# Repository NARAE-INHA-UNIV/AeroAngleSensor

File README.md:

# AeroAngleSensor

[[Youtube] 무인 항공기용 회전각 센서 시현 영상](https://www.youtube.com/watch?v=Au1dN9QMTIA)

- 일시 : 2025 1학기
- 팀명 : 항공전자, 각도발전소(인하종합설계경진대회)
- 팀장 : 김정걸
- 팀원 : 김성호, 임정섭, 이해강, 이현제

## 프로젝트 구조

```
AeroAngleSensor/
├── AeroAngleSense        # KiCAD 회로
├── AeroAngleSense.step   # 센서 step 파일
├── docs                  # docs 문서 및 이미지 에셋
├── Firmware              # 펌웨어 STM32 코드
├── LICENSE.md
├── README.md
└── Schematic.pdf
```

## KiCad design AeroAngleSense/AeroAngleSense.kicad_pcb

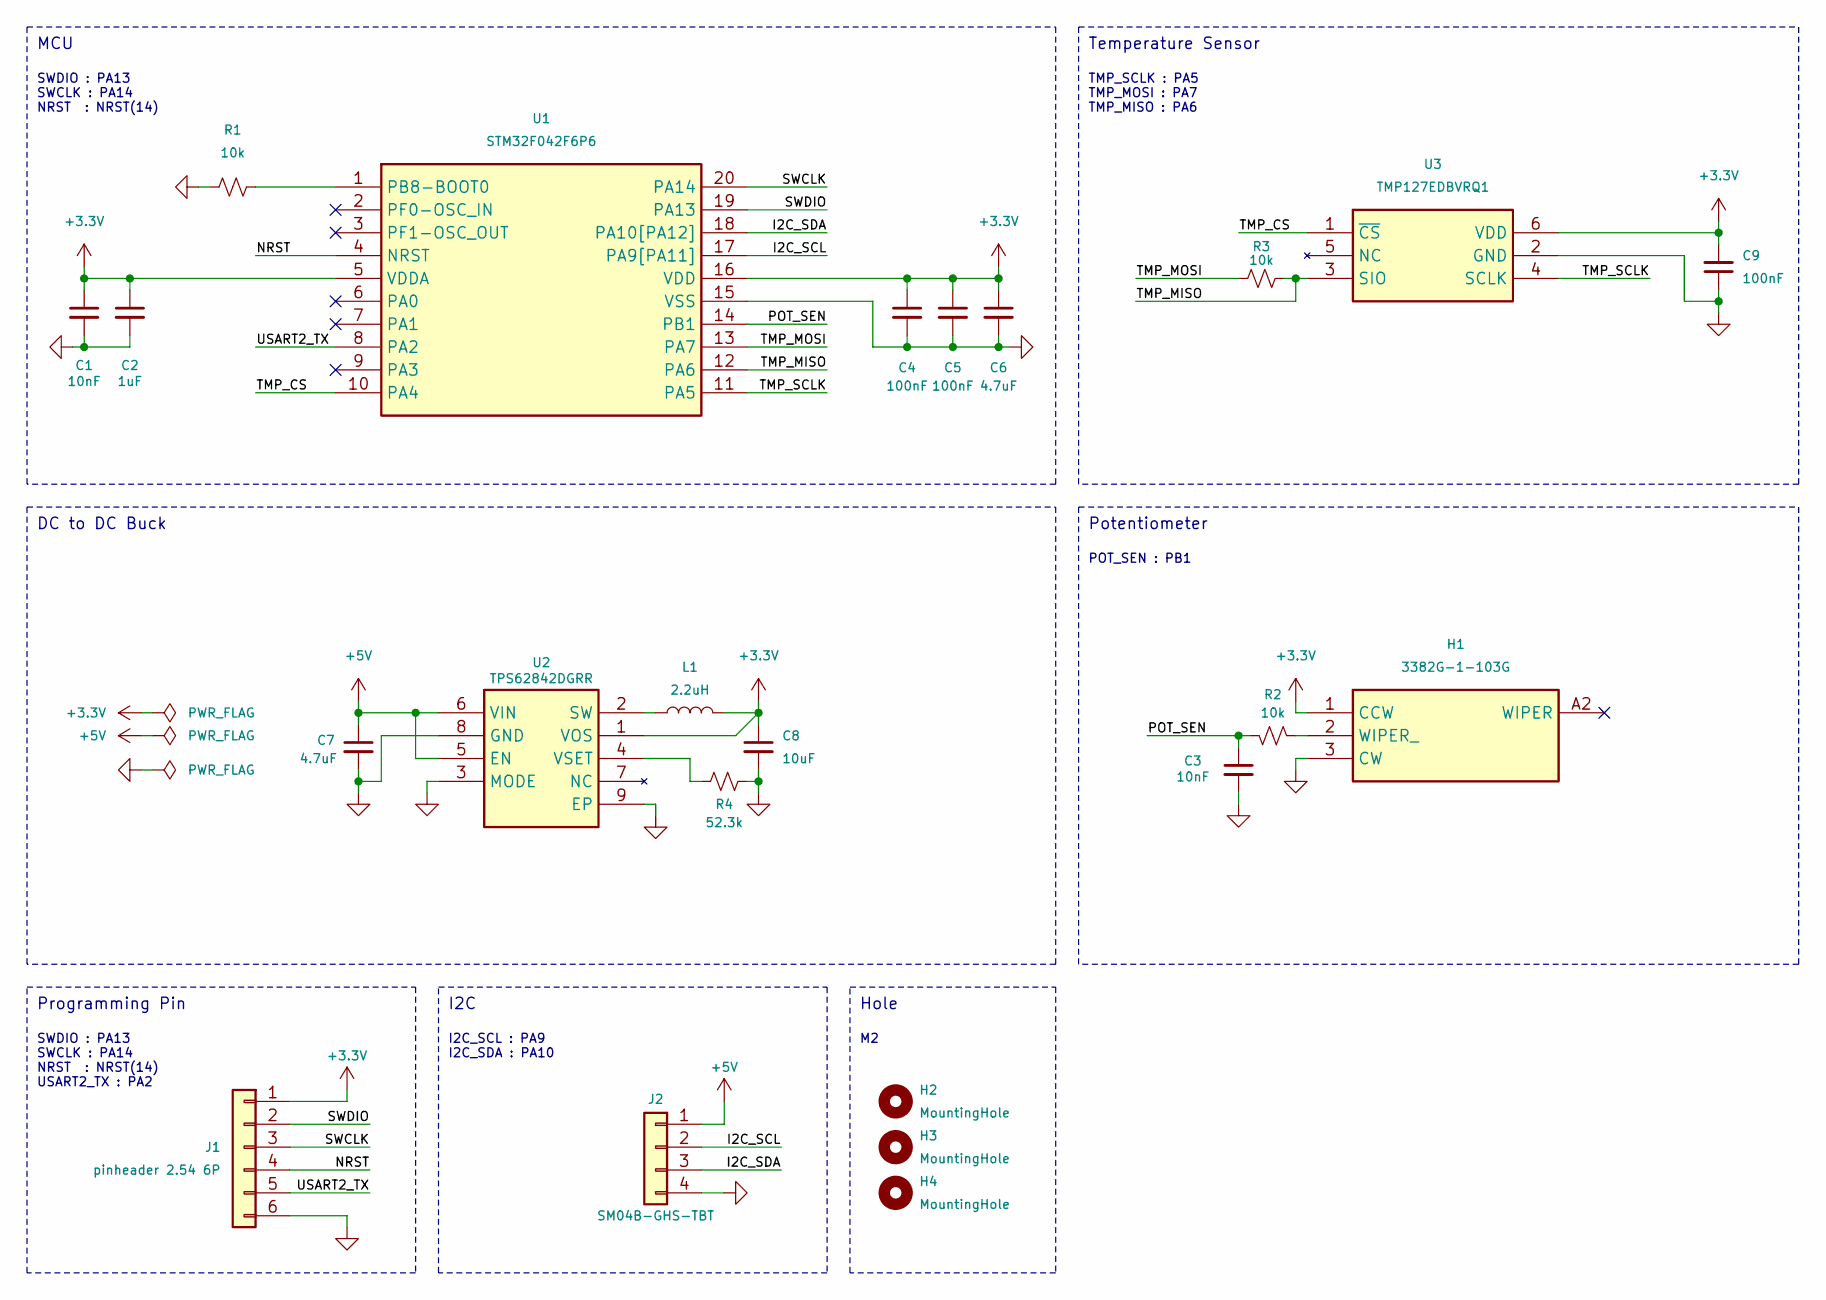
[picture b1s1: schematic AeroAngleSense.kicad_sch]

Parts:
C1, C3: 10nF; C_0603_1608Metric; LCSC C1589
C2: 1uF; C_0603_1608Metric; LCSC C1592
C4, C5, C9: 100nF; C_0603_1608Metric; LCSC C1590
C6, C7: 4.7uF; C_0603_1608Metric; LCSC C1705
C8: 10uF; C_0603_1608Metric; LCSC C1691
H1: 3382G-1-103G; 3382G1103G; Mouser Part Number 652-3382G-1-103G
H2, H3, H4: MountingHole; MountingHole_2.2mm_M2_Pad
J1: pinheader 2.54 6P; PinHeader_1x06_P2.54mm_Vertical
J2: SM04B-GHS-TBT; JST_GH_SM04B-GHS-TB_04x1.25mm_Angled; LCSC C189895
L1: 2.2uH; VLS201610ET-2R2M; LCSC C136230
R1, R2, R3: 10k; R_0603_1608Metric; LCSC C15401
R4: 52.3k; R_0603_1608Metric; LCSC C23198
U1: STM32F042F6P6; Manufacturer_Part_Number STM32F042F6P6; Mouser Part Number 511-STM32F042F6P6
U2: TPS62842DGRR; Mouser Part Number 595-TPS62842DGRR
U3: TMP127EDBVRQ1; SOT95P280X145-6N; Mouser Part Number 595-TMP127EDBVRQ1

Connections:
+3.3V: C1.1, C2.1, C4.1, C5.1, C6.1, C8.1, C9.2, H1.1 (CCW), J1.1, L1.2, U1.5 (VDDA), U1.16 (VDD), U2.1 (VOS), U3.6 (VDD)
+5V: C7.1, J2.1, U2.5 (EN), U2.6 (VIN)
/I2C_SCL: J2.2, U1.17 (PA9[PA11])
/I2C_SDA: J2.3, U1.18 (PA10[PA12])
/NRST: J1.4, U1.4 (NRST)
/POT_SEN: C3.1, R2.2, U1.14 (PB1)
/SWCLK: J1.3, U1.20 (PA14)
/SWDIO: J1.2, U1.19 (PA13)
/TMP_CS: U1.10 (PA4), U3.1 (~CS)
/TMP_MISO: R3.2, U1.12 (PA6), U3.3 (SIO)
/TMP_MOSI: R3.1, U1.13 (PA7)
/TMP_SCLK: U1.11 (PA5), U3.4 (SCLK)
/USART2_TX: J1.5, U1.8 (PA2)
GND: C1.2, C2.2, C3.2, C4.2, C5.2, C6.2, C7.2, C8.2, C9.1, H1.3 (CW), J1.6, J2.4, R1.1, R4.2, U1.15 (VSS), U2.3 (MODE), U2.8 (GND), U2.9 (EP), U3.2 (GND)
unnamed: H1.2 (WIPER_), R2.1
unnamed: R1.2, U1.1 (PB8-BOOT0)
unnamed: L1.1, U2.2 (SW)
unnamed: R4.1, U2.4 (VSET)

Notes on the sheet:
I2C_SCL : PA9 I2C_SDA : PA10
I2C
TMP_SCLK : PA5 TMP_MOSI : PA7 TMP_MISO : PA6
DC to DC Buck
SWDIO : PA13 SWCLK : PA14 NRST : NRST(14)
MCU
Programming Pin
Temperature Sensor
POT_SEN : PB1
SWDIO : PA13 SWCLK : PA14 NRST : NRST(14) USART2_TX : PA2
Potentiometer
Hole

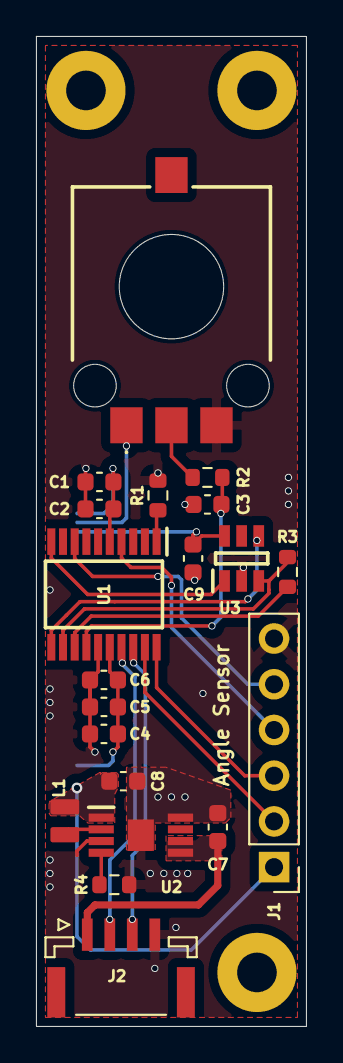
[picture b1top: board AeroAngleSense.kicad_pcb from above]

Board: 2 copper layers, 15.0 x 55.0 mm, 23 parts (0 on the bottom side), 18 nets.

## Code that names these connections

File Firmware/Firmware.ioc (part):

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Mcu.Name=STM32F042F6Px
Mcu.Package=TSSOP20
Mcu.UserName=STM32F042F6Px
PA10.Mode=I2C
PA10.Signal=I2C1_SDA
PA2.Mode=Asynchronous
PA2.Signal=USART2_TX
PA3.Mode=Asynchronous
PA3.Signal=USART2_RX
PA4.GPIOParameters=GPIO_Label
PA4.GPIO_Label=TMP_CS
PA4.Signal=GPIO_Output
PA5.Mode=Full_Duplex_Slave
PA5.Signal=SPI1_SCK
PA6.Mode=Full_Duplex_Slave
PA6.Signal=SPI1_MISO
PA7.Mode=Full_Duplex_Slave
PA7.Signal=SPI1_MOSI
PA9.Mode=I2C
PA9.Signal=I2C1_SCL
PB1.GPIOParameters=GPIO_Label
PB1.GPIO_Label=POT_SEN
PB1.Signal=SharedAnalog_PB1
board=custom

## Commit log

2025-08-06 kicad 초기 업로드
2025-08-06 init
2025-08-06 스케메틱 및 라이브러리 파일 최초 업로드
2025-08-12 fix:temp spi 3 wire/pot_sen symbol
2025-08-12 LCSC값 추가
2025-08-12 add:DEBUG&I2C conn
2025-08-19 소자 배치
2025-08-19 배선 연결 작업_1
2025-08-21 pcb layout done.
2025-08-21 add : copper zone"
2025-08-22 배선 작업_1
2025-08-24 배선_2
2025-08-25 배선_3
2025-08-25 배선 최종
2025-08-25 배선_4
2025-08-28 fix : route
2025-08-28 rm : useless files
2025-08-28 fix : silkscreen
2025-08-31 fix:readme
2025-09-09 add : firmware code - ADC, I2C send
